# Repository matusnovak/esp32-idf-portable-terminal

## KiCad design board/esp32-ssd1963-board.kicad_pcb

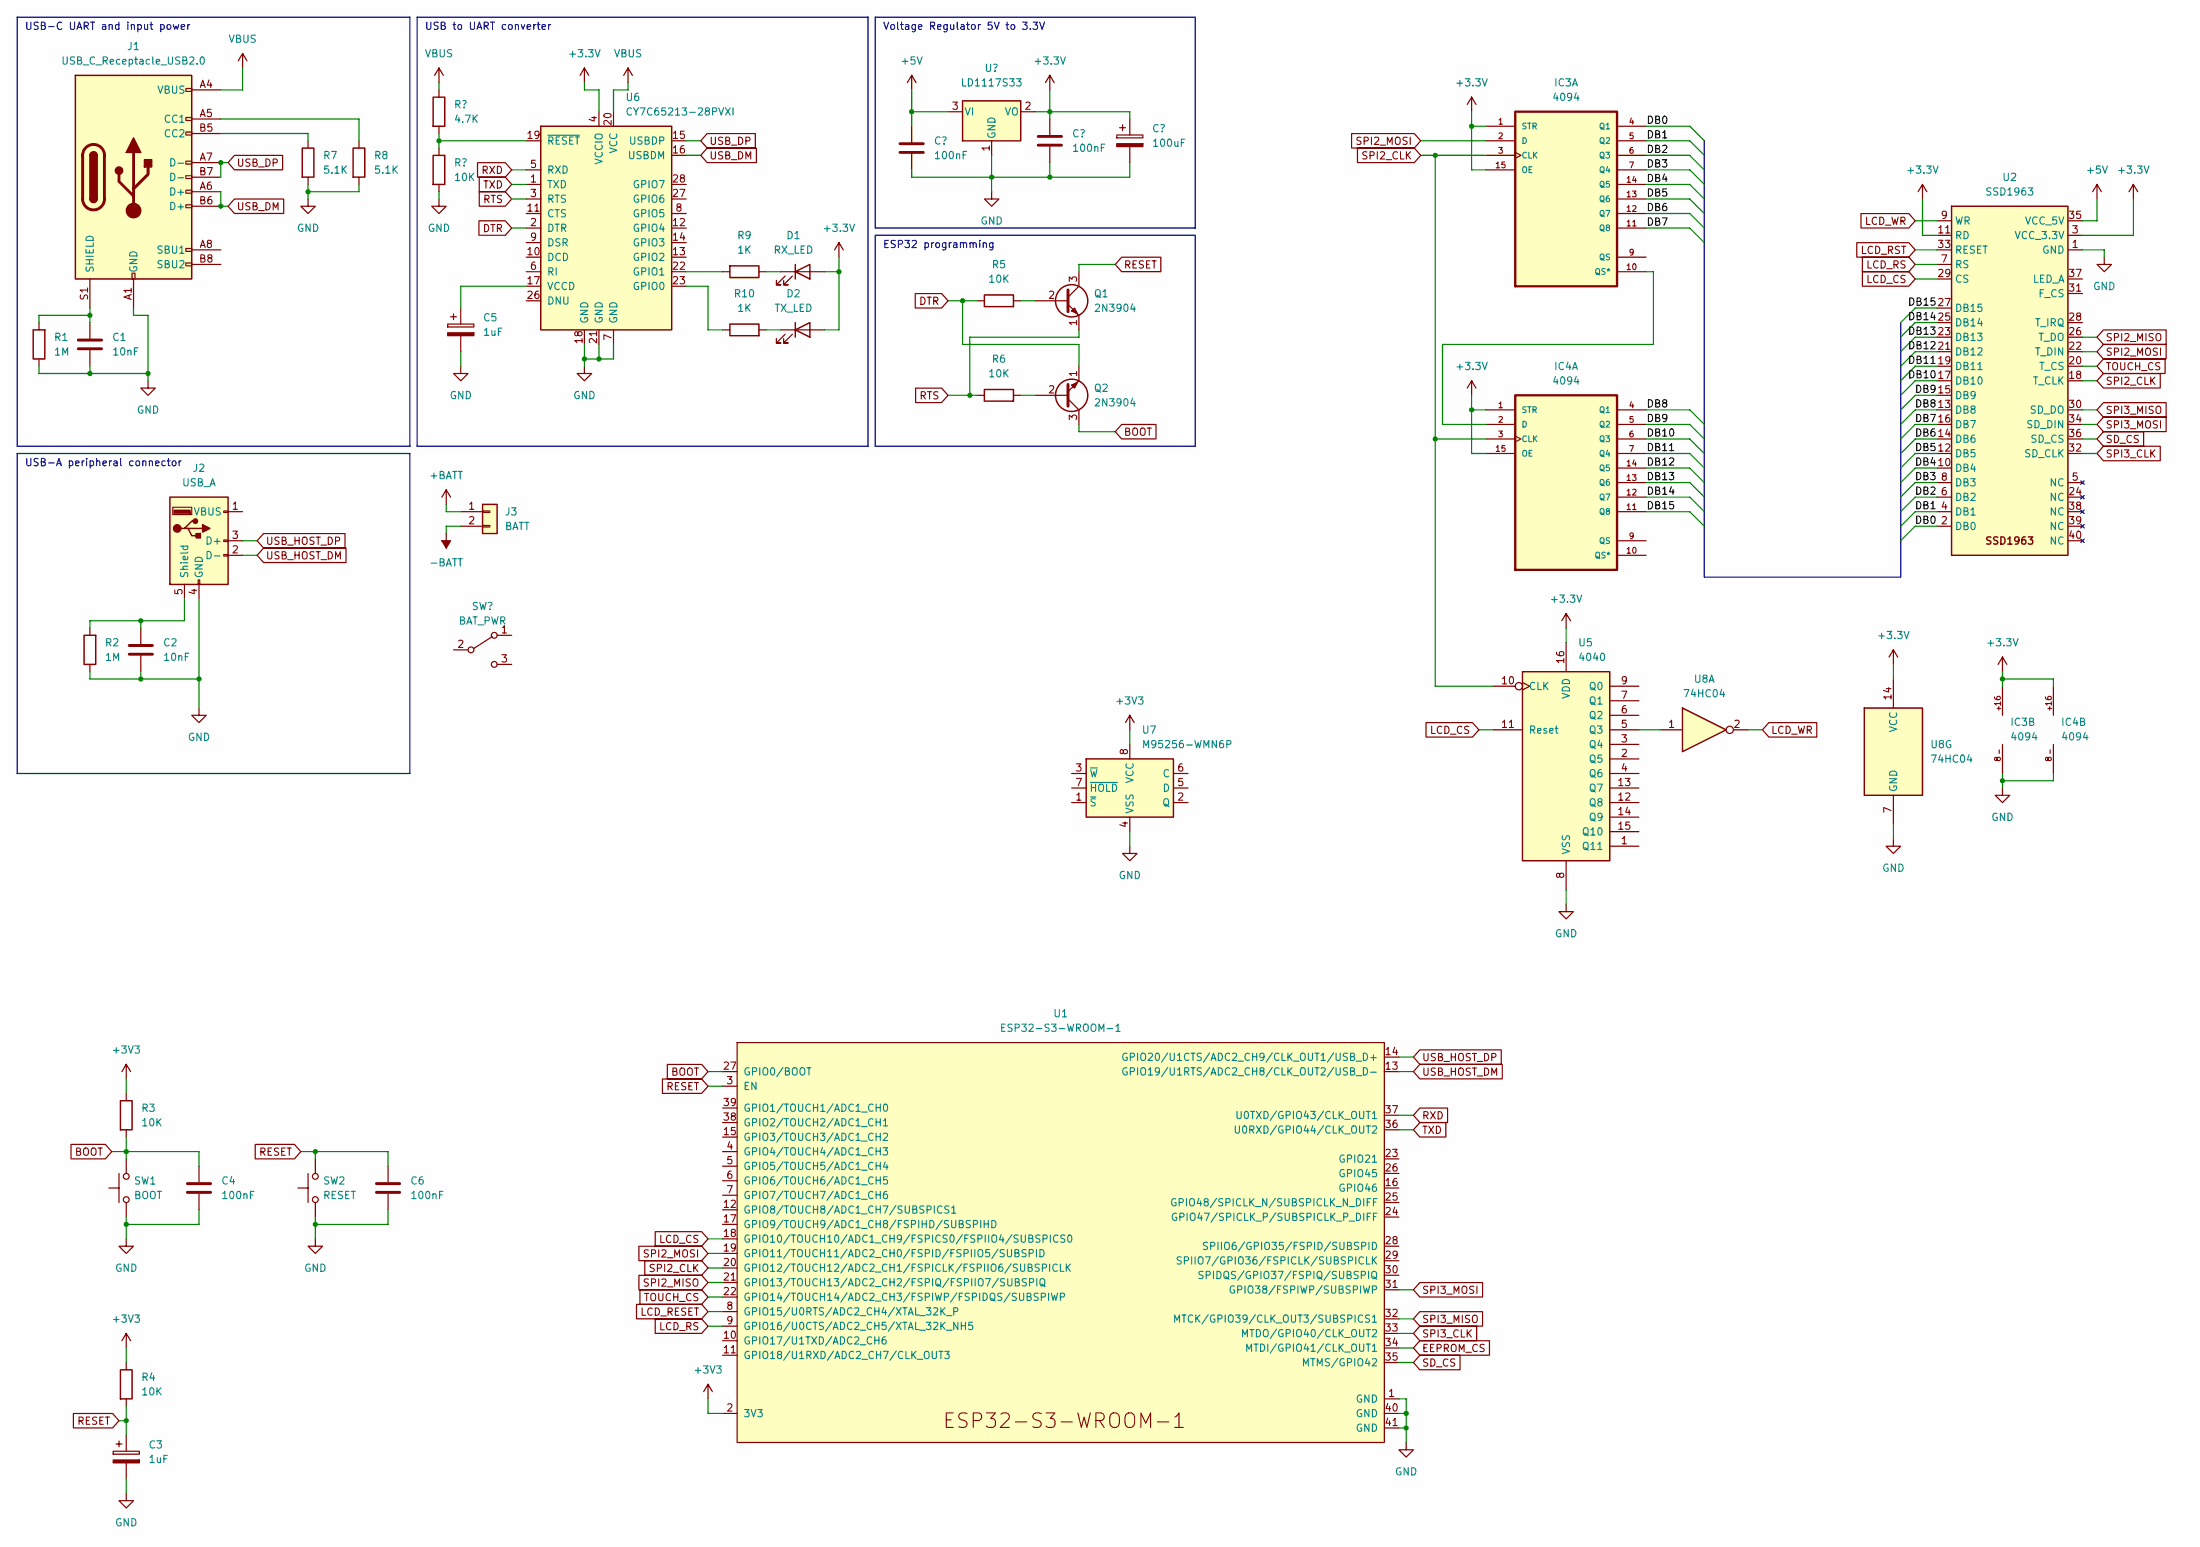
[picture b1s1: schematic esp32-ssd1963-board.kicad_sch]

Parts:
C1, C2: 10nF; C_1206_3216Metric_Pad1.33x1.80mm_HandSolder
C3, C5: 1uF; CP_Elec_4x5.7
C4, C6: 100nF; C_1206_3216Metric_Pad1.33x1.80mm_HandSolder
D1: RX_LED; LED_1206_3216Metric_Pad1.42x1.75mm_HandSolder
D2: TX_LED; LED_1206_3216Metric_Pad1.42x1.75mm_HandSolder
IC3, IC4: 4094; SO-16_3.9x9.9mm_P1.27mm
J1: USB_C_Receptacle_USB2.0; USB_C_Receptacle_Palconn_UTC16-G
J2: USB_A; USB_A_CONNFLY_DS1095-WNR0
J3: BATT
Q1, Q2: 2N3904; TO-92_Inline
R1, R2: 1M; R_1206_3216Metric_Pad1.30x1.75mm_HandSolder
R3, R4, R5, R6: 10K; R_1206_3216Metric_Pad1.30x1.75mm_HandSolder
R7, R8: 5.1K; R_1206_3216Metric_Pad1.30x1.75mm_HandSolder
R9, R10: 1K; R_1206_3216Metric_Pad1.30x1.75mm_HandSolder
SW1: BOOT; SW_PUSH_6mm
SW2: RESET; SW_PUSH_6mm
U1: ESP32-S3-WROOM-1
U2: SSD1963
U5: 4040; SO-16_3.9x9.9mm_P1.27mm
U6: CY7C65213-28PVXI; SSOP-28_5.3x10.2mm_P0.65mm
U7: M95256-WMN6P; SOIC-8_3.9x4.9mm_P1.27mm
U8: 74HC04; SO-14_3.9x8.65mm_P1.27mm

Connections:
+3.3V: D1.2 (A), D2.2 (A), IC3.1 (STR), IC3.15 (OE), IC3.16, IC4.1 (STR), IC4.15 (OE), IC4.16, U2.3 (VCC_3.3V), U2.11 (RD), U5.16 (VDD), U6.4 (VCCIO), U8.14 (VCC)
+3V3: R3.1, R4.1, U1.2 (3V3), U7.8 (VCC); also elsewhere on the board
+5V: U2.35 (VCC_5V)
/DB0: IC3.4 (Q1), U2.2 (DB0)
/DB1: IC3.5 (Q2), U2.4 (DB1)
/DB2: IC3.6 (Q3), U2.6 (DB2)
/DB3: IC3.7 (Q4), U2.8 (DB3)
/DB4: IC3.14 (Q5), U2.10 (DB4)
/DB5: IC3.13 (Q6), U2.12 (DB5)
/DB6: IC3.12 (Q7), U2.14 (DB6)
/DB7: IC3.11 (Q8), U2.16 (DB7)
/DB8: IC4.4 (Q1), U2.13 (DB8)
/DB9: IC4.5 (Q2), U2.15 (DB9)
/DB10: IC4.6 (Q3), U2.17 (DB10)
/DB11: IC4.7 (Q4), U2.19 (DB11)
/DB12: IC4.14 (Q5), U2.21 (DB12)
/DB13: IC4.13 (Q6), U2.23 (DB13)
/DB14: IC4.12 (Q7), U2.25 (DB14)
/DB15: IC4.11 (Q8), U2.27 (DB15)
BOOT: C4.1, Q2.3 (C), R3.2, SW1.2, U1.27 (GPIO0/BOOT)
DTR: Q2.1 (E), R5.1, U6.2 (DTR)
EEPROM_CS: U1.34 (MTDI/GPIO41/CLK_OUT1)
GND: C1.2, C2.2, C3.2, C4.2, C5.2, C6.2, IC3.8, IC4.8, J1.A1 (GND), J1.A12 (GND), J1.B1 (GND), J1.B12 (GND), J2.4 (GND), R1.1, R2.1, R7.2, R8.2, SW1.1, SW2.1, U1.1 (GND), U1.40 (GND), U1.41 (GND), U2.1 (GND), U5.8 (VSS), U6.7 (GND), U6.18 (GND), U6.21 (GND), U7.4 (VSS), U8.7 (GND); also elsewhere on the board
LCD_CS: U1.18 (GPIO10/TOUCH10/ADC1_CH9/FSPICS0/FSPIIO4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), U2.29 (CS), U5.11 (Reset)
LCD_RESET: U1.8 (GPIO15/U0RTS/ADC2_CH4/XTAL_32K_P)
LCD_RS: U1.9 (GPIO16/U0CTS/ADC2_CH5/XTAL_32K_NH5), U2.7 (RS)
LCD_RST: U2.33 (RESET)
LCD_WR: U2.9 (WR), U8.2
unnamed: C1.1, J1.S1 (SHIELD), R1.2
unnamed: C2.1, J2.5 (Shield), R2.2
unnamed: C5.1, U6.17 (VCCD)
unnamed: D1.1 (K), R9.1
unnamed: D2.1 (K), R10.2
unnamed: IC3.10 (QS*), IC4.2 (D)
unnamed: J1.A5 (CC1), R8.1
unnamed: J1.B5 (CC2), R7.1
unnamed: Q1.2 (B), R5.2
unnamed: Q2.2 (B), R6.2
unnamed: U5.5 (Q3), U8.1
RESET: C3.1, C6.1, Q1.3 (C), R4.2, SW2.2, U1.3 (EN)
RTS: Q1.1 (E), R6.1, U6.3 (RTS)
RXD: U1.37 (U0TXD/GPIO43/CLK_OUT1), U6.5 (RXD)
SD_CS: U1.35 (MTMS/GPIO42), U2.36 (SD_CS)
SPI2_CLK: IC3.3 (CLK), IC4.3 (CLK), U1.20 (GPIO12/TOUCH12/ADC2_CH1/FSPICLK/FSPIIO6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), U2.18 (T_CLK), U5.10 (CLK)
SPI2_MISO: U1.21 (GPIO13/TOUCH13/ADC2_CH2/FSPIQ/FSPIIO7/S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), U2.26 (T_DO)
SPI2_MOSI: IC3.2 (D), U1.19 (GPIO11/TOUCH11/ADC2_CH0/FSPID/FSPIIO5/S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), U2.22 (T_DIN)
SPI3_CLK: U1.33 (MTDO/GPIO40/CLK_OUT2), U2.32 (SD_CLK)
SPI3_MISO: U1.32 (MTCK/GPIO39/CLK_OUT3/SUBSPICS1), U2.30 (SD_DO)
SPI3_MOSI: U1.31 (GPIO38/FSPIWP/SUBSPIWP), U2.34 (SD_DIN)
TOUCH_CS: U1.22 (GPIO14/TOUCH14/ADC2_CH3/FSPIWP/FSPIDQS/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), U2.20 (T_CS)
TXD: U1.36 (U0RXD/GPIO44/CLK_OUT2), U6.1 (TXD)
USB_DM: J1.A6 (D+), J1.B6 (D+), U6.16 (USBDM)
USB_DP: J1.A7 (D-), J1.B7 (D-), U6.15 (USBDP)
USB_HOST_DM: J2.2 (D-), U1.13 (GPIO19/U1RTS/ADC2_CH8/CLK_OUT2/USB_D-)
USB_HOST_DP: J2.3 (D+), U1.14 (GPIO20/U1CTS/ADC2_CH9/CLK_OUT1/USB_D+)
VBUS: J1.A4 (VBUS), J1.A9 (VBUS), J1.B4 (VBUS), J1.B9 (VBUS), U6.20 (VCC)

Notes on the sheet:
USB-A peripheral connector
ESP32 programming
Voltage Regulator 5V to 3.3V
USB to UART converter
USB-C UART and input power

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
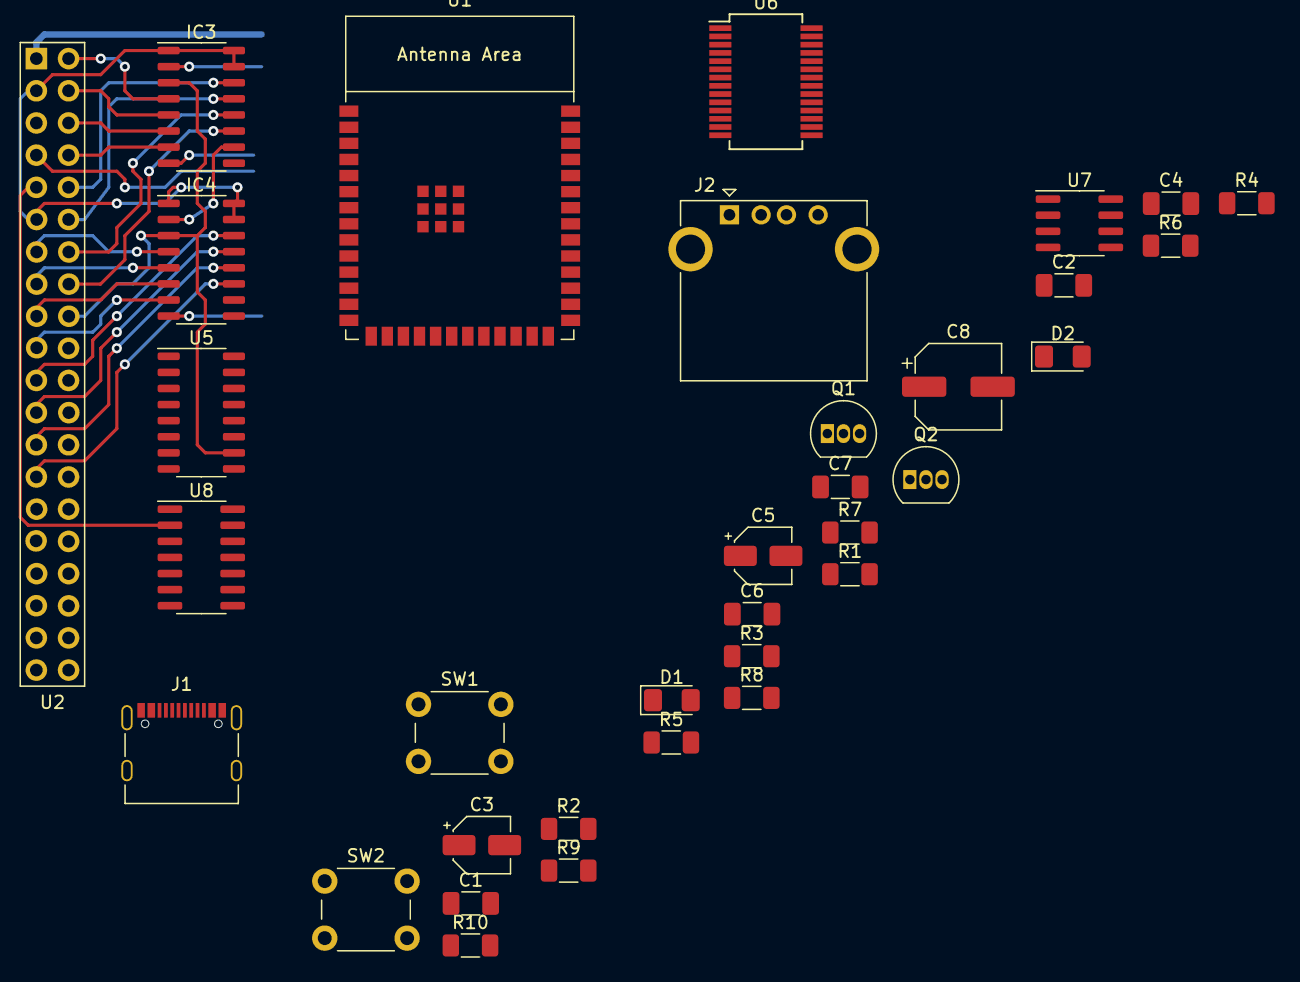
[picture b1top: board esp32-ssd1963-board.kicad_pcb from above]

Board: 2 copper layers, 34 parts (0 on the bottom side), 54 nets.

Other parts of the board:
C7: 100nF; C_1206_3216Metric_Pad1.33x1.80mm_HandSolder
C8: 47uF; CP_Elec_6.3x5.7

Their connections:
+3V3: C7.1, C8.1; also elsewhere on the board
GND: C7.2, C8.2; also elsewhere on the board

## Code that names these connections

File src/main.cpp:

#include <string.h>
#include <driver/gpio.h>
#include <driver/i2c.h>
#include <driver/spi_master.h>
#include <freertos/FreeRTOS.h>
#include <freertos/task.h>
#include <esp_system.h>
#include <esp_wifi.h>
#include <esp_event.h>
#include <esp_log.h>
#include <nvs_flash.h>
#include <lwip/err.h>
#include <lwip/sys.h>
#include <m95_eeprom.hpp>
#include <ssd1963.hpp>
#include <hr2046.hpp>

extern "C" {
    void app_main();
}

static const char *TAG = "example";

#define ESP_INTR_FLAG_DEFAULT 0

#define SPI2_PIN_MISO 13
#define SPI2_PIN_MOSI 11
#define SPI2_PIN_CLK 12
#define SPI2_PIN_CS0 10
#define SPI2_PIN_CS1 15

#define SPI3_PIN_MISO 39
#define SPI3_PIN_MOSI 38
#define SPI3_PIN_CLK 40
#define SPI3_PIN_CS0 41
#define SPI3_PIN_CS1 42

#define EEPROM_CS SPI3_PIN_CS0
#define LCD_BUS_CS SPI2_PIN_CS0
#define LCD_RESET 7
#define LCD_CS 6
#define LCD_WR 5
#define LCD_RS 4

#define TOUCH_CS SPI2_PIN_CS1
#define TOUCH_IRQ 3

void led_blink_task(void *pvParameter) {
    // gpio_reset_pin(GPIO_NUM_10);
    gpio_pad_select_gpio(GPIO_NUM_10);
    gpio_set_direction(GPIO_NUM_10, GPIO_MODE_OUTPUT);

    while (1) {
        gpio_set_level(GPIO_NUM_10, 1);
        vTaskDelay(100 / portTICK_PERIOD_MS);

        gpio_set_level(GPIO_NUM_10, 0);
        vTaskDelay(100 / portTICK_PERIOD_MS);
    }
}

/*void print_task(void *pvParameter) {
 
	while(1) {
	    printf("Hello world 42!\n");
	    vTaskDelay(1000 / portTICK_RATE_MS);
	}
}*/

void eepromTest(void *pvParameter) {
    spi_bus_config_t bus = {};
    bus.data0_io_num = -1;
    bus.data1_io_num = -1;
    bus.data2_io_num = -1;
    bus.data3_io_num = -1;
    bus.data4_io_num = -1;
    bus.data5_io_num = -1;
    bus.data6_io_num = -1;
    bus.data7_io_num = -1;
    bus.miso_io_num = SPI3_PIN_MISO;
    bus.mosi_io_num = SPI3_PIN_MOSI;
    bus.sclk_io_num = SPI3_PIN_CLK;
    bus.quadhd_io_num = -1;
    bus.quadwp_io_num = -1;
    bus.max_transfer_sz = 4;

    printf("spi_bus_initialize SPI3_HOST\n");
    auto ret = spi_bus_initialize(SPI3_HOST, &bus, SPI_DMA_CH_AUTO);
    ESP_ERROR_CHECK(ret);

    printf("EEPROM initializing...\n");
    M95EEPROM eeprom{SPI3_HOST, EEPROM_CS, 24};
    printf("EEPROM initialized!\n");

    eeprom.writeByte(0x00, 44);
    eeprom.writeByte(0x01, 24);

    uint8_t b0;
    uint8_t b1;
    eeprom.readByte(0x00, &b0);
    eeprom.readByte(0x01, &b1);
    printf("EEPROM read: [%d, %d]\n", b0, b1);

    static const auto str = "Hello World!";
    eeprom.writeRange(0x05, reinterpret_cast<const uint8_t*>(str), strlen(str));

    char buffer[24];
    eeprom.readRange(0x05, reinterpret_cast<uint8_t*>(buffer), strlen(str));

    printf("EEPROM read range: [%s]\n", buffer);

    while (1) {
        // Add your main loop handling code here.
        vTaskDelay(500 / portTICK_PERIOD_MS);
    }
}

void lcdTest(void *pvParameter) {
    spi_bus_config_t bus = {};
    bus.data0_io_num = -1;
    bus.data1_io_num = -1;
    bus.data2_io_num = -1;
    bus.data3_io_num = -1;
    bus.data4_io_num = -1;
    bus.data5_io_num = -1;
    bus.data6_io_num = -1;
    bus.data7_io_num = -1;
    bus.miso_io_num = SPI2_PIN_MISO;
    bus.mosi_io_num = SPI2_PIN_MOSI;
    bus.sclk_io_num = SPI2_PIN_CLK;
    bus.quadhd_io_num = -1;
    bus.quadwp_io_num = -1;
    bus.max_transfer_sz = 4;

    printf("spi_bus_initialize SPI2_HOST\n");
    auto ret = spi_bus_initialize(SPI2_HOST, &bus, SPI_DMA_CH_AUTO);
    ESP_ERROR_CHECK(ret);

    ssd1963_handle_t lcd;
    ssd1963_config_t config = {};
    config.bus_host = SPI2_HOST;
    config.bus_cs_pin = LCD_BUS_CS;
    config.cs_pin = LCD_CS;
    config.reset_pin = LCD_RESET;
    config.rs_pin = LCD_RS;
    config.wr_pin = LCD_WR;
    config.width = 800;
    config.height = 480;

    printf("ssd1963_init\n");
    ret = ssd1963_init(&config, &lcd);
    ESP_ERROR_CHECK(ret);

    printf("ssd1963_reset\n");
    ret = ssd1963_reset(lcd);
    ESP_ERROR_CHECK(ret);

    printf("ssd1963_enable\n");
    ret = ssd1963_enable(lcd);
    ESP_ERROR_CHECK(ret);

    /*printf("ssd1963_fill_rect\n");
    ssd1963_fill_rect(lcd, (800 / 6) * 0, 0, 800 / 6, 480, rgb_color_16(255, 0, 0));
    ssd1963_fill_rect(lcd, (800 / 6) * 1, 0, 800 / 6, 480, rgb_color_16(0, 255, 0));
    ssd1963_fill_rect(lcd, (800 / 6) * 2, 0, 800 / 6, 480, rgb_color_16(0, 0, 255));
    ssd1963_fill_rect(lcd, (800 / 6) * 3, 0, 800 / 6, 480, rgb_color_16(255, 255, 255));
    ssd1963_fill_rect(lcd, (800 / 6) * 4, 0, 800 / 6, 480, rgb_color_16(127, 127, 127));
    ssd1963_fill_rect(lcd, (800 / 6) * 5, 0, 800 / 6, 480, rgb_color_16(0, 0, 0));*/

    //ssd1963_fill_test(lcd);

    printf("ssd1963 DONE\n");

    /*hr2046_config_t touch_config = {};
    touch_config.spi_host = SPI2_HOST;
    touch_config.cs_pin = TOUCH_CS;
    touch_config.irq_pin = TOUCH_IRQ;

    hr2046_handle_t touch;
    
    ret = hr2046_init(&touch_config, &touch);
    ESP_ERROR_CHECK(ret);

    ret = hr2046_power_down(touch);
    ESP_ERROR_CHECK(ret);*/

    while (1) {
        vTaskDelay(100 / portTICK_PERIOD_MS);

        /*uint16_t touch_values[2];
        hr2046_read(touch, HR2046_CH_X, &touch_values[0]);
        hr2046_read(touch, HR2046_CH_X, &touch_values[0]);
        hr2046_read(touch, HR2046_CH_Y, &touch_values[1]);*/

        // hr2046_has_touch(touch, &touched);

        //printf("Touch: [%d, %d]\n", touch_values[0], touch_values[1]);

        /*
        uint16_t touch_values[3];
        hr2046_read_xyz(touch, &touch_values[0], &touch_values[1], &touch_values[2]);

        printf("Touch: [%d, %d] %d\n", touch_values[0], touch_values[1], touch_values[2]);
        */
    }
}

void app_main() {
    printf("app_main!\n");
    nvs_flash_init();

    //install gpio isr service
    auto ret = gpio_install_isr_service(ESP_INTR_FLAG_DEFAULT);
    ESP_ERROR_CHECK(ret);

    // Initialize NVS
    /*esp_err_t ret = nvs_flash_init();
    if (ret == ESP_ERR_NVS_NO_FREE_PAGES || ret == ESP_ERR_NVS_NEW_VERSION_FOUND)
    {
        ESP_ERROR_CHECK(nvs_flash_erase());
        ret = nvs_flash_init();
    }
    ESP_ERROR_CHECK(ret);*/

    ESP_LOGI(TAG, "Starting blink");
    //xTaskCreate(&led_blink_task, "led_blink_task", 2048, NULL, 5, NULL);
    //xTaskCreate(&print_task, "print_task", 2048, NULL, 5, NULL);
    //xTaskCreate(&eepromTest, "eepromTest", 8192, NULL, 4, NULL);
    xTaskCreate(&lcdTest, "lcdTest", 8192, NULL, 5, NULL);
}

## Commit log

2022-12-19 Add board files
